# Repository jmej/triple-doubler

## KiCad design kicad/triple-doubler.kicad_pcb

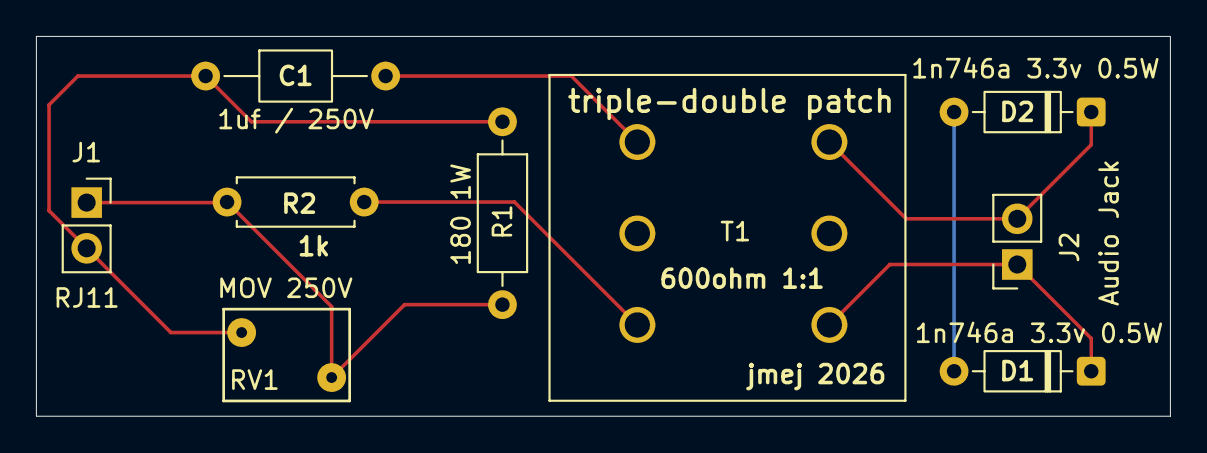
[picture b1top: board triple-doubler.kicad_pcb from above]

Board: 2 copper layers, 63.0 x 21.1 mm, 9 parts (0 on the bottom side), 7 nets.

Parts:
C1: 1uf / 250V; C_Axial_L3.8mm_D2.6mm_P10.00mm_Horizontal
D1, D2: 1n746a 3.3v 0.5W; D_DO-35_SOD27_P7.62mm_Horizontal
J1: RJ11; PinSocket_1x02_P2.54mm_Vertical
J2: Audio Jack; PinSocket_1x02_P2.54mm_Vertical
R1: 180 1W; R_Axial_DIN0207_L6.3mm_D2.5mm_P10.16mm_Horizontal
R2: 1k; R_Axial_DIN0207_L6.3mm_D2.5mm_P7.62mm_Horizontal
RV1: MOV 250V; RV_Disc_D7mm_W5.1mm_P5mm
T1: TA-30-01; Transformer TA-30-1 telephone 600ohm

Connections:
unnamed: C1.1, J1.2, R1.1, RV1.1
unnamed: D1.2 (A), D2.2 (A)
unnamed: D1.1 (K), J2.1, T1.4 (SB)
unnamed: D2.1 (K), J2.2, T1.6 (SA)
unnamed: J1.1, R1.2, R2.1, RV1.2
unnamed: C1.2, T1.1 (AA)
unnamed: R2.2, T1.3 (AB)

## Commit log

2026-05-08 repo reorg - adds docs
2026-05-08 updates footprint and starts layout
2026-05-09 layout mostly done
2026-05-13 minor tweaks, production gerbers
